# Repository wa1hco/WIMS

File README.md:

# WS Hub

WS Hub (formerly WIMS, the WSJT-X Instance Management System) is one console for a station running several copies of WSJT-X. It gathers every decode into one ranked **call roster**, marks what your goal still needs, and lets one operator answer a station with a click. It works alongside N1MM Logger+, GridTracker, DX cluster spots, and rotators.

It is built for multi-multi VHF contesting (the ARRL VHF contests at W2SZ), and it is useful at home with one radio too: a contest, an award such as DXCC or VUCC, or just a checklist of what is worth working.

**A person starts every transmit.** WS Hub never calls CQ and never transmits on its own. Clicking a roster line answers a station that WSJT-X has already decoded; Enable TX and CQ stay in WSJT-X. It also keeps radios that share an antenna or band from transmitting at the same time.

*The Operate page (an October screenshot, before the WS Hub name and the Show menu).*

## Install

Download the newest release from **[GitHub Releases](https://github.com/wa1hco/WS-Hub/releases)**. The files are still named `wims-<version>-…`.

- **Linux:** unpack the `.tar.gz` anywhere, open **scripts**, and double-click **Install WS Hub**. If the file manager asks, choose **Allow Launching** (or Execute, or Run). WS Hub copies itself to `~/.local/share/ws-hub`; delete the download, then double-click **WS Hub**.
- **Windows:** extract the `.zip` to `C:\WIMS`, open `scripts\windows`, and double-click **Install-Wims.cmd**. Then double-click **WS Hub** on the Desktop.

Step by step, with what to do when the desktop asks a question: **[INSTALL.md](INSTALL.md)**. Updates come from the **Updates** list in the WS Hub window.

## What it does today

- **Call roster** on the Operate page: every decode from every WSJT-X, ranked by score, with Country, distance, and heading. A badge says why a station is needed (grid, state, DXCC, CQ zone, ITU zone, continent, or call); in a contest it says **mult**. Click a line to **Work** that station in the WSJT-X that heard it; **Halt TX** stops what your console started.
- **Goals:** a contest, an award (DXCC, Worked All States, VUCC), a checklist, or your own list, checked against the log you choose. WS Hub reads logs and never changes them.
- **Spotted:** DX cluster spots the goal still needs, on any band, filtered by mode (SSB, CW, FT8, FT4, Other). A spot on a band with no WSJT-X running is marked **QSY**. A click selects the station; it does not retune or transmit yet.
- **Headings:** from the grid when one is known; otherwise an approximate heading from the station's country, marked `~`. WS Hub never guesses a grid square.
- **N1MM:** digital contacts go into N1MM, and N1MM's log decides dupes and mults.
- **Transmit interlock:** radios in one group never transmit together, and an SSB/CW key line can hold a patched WSJT-X off the air.
- **Rotators:** headings are read through hamlib `rotctld`.

What is planned and not built yet (for example, a spot click that retunes the radio and points the antenna) is in **[the build status](docs/plan/wims_status.md)**.

## Documentation

| For | Read |
|--|--|
| Installing | [INSTALL.md](INSTALL.md) |
| Using the console | [User manual](docs/User-manual.md) |
| Setting up WSJT-X, N1MM, and the key line | [Operator setup](docs/operator_setup.md) |
| Trying it at home, step by step | [Tester quick start](docs/tester_quickstart.md) · [What each piece is](docs/tester_roles.md) |
| Every file you can double-click | [scripts/README.md](scripts/README.md) |
| Networking a multi-PC station | [Networking](docs/plan/wims_networking.md) |
| How it is designed, and what is built | [Design](docs/plan/wims_design.md) · [Build status](docs/plan/wims_status.md) |
| What changed in each version | [Release notes](docs/releases/) |

Inside the program, the code, folders, and files still use the old name `wims` (for example `src/wims` and `C:\WIMS`). That is expected.

## Developer

For people changing WS Hub. Operators use the desktop icon.

WS Hub is plain Python 3.10+ with no packages to install. The code is in `src/`. From a clone of [wa1hco/WS-Hub](https://github.com/wa1hco/WS-Hub):

```bash
export PYTHONPATH=$PWD/src   # the launch scripts in scripts/ set this themselves
python3 -m wims version
python3 -m wims solo --no-open
tools/dev/validate.sh        # the same checks CI runs
```

On a Mac there is no double-click installer; from the folder run `scripts/add-wims-to-desktop.sh`. Cutting a release: [INSTALL.md](INSTALL.md#cut-a-release-maintainers). Rules for changes (safety, wording, tests): [docs/project_rules.md](docs/project_rules.md).

## License

WS Hub is free software under the **GNU General Public License v3.0 or later** (GPL-3.0-or-later). See [LICENSE](LICENSE).

    Copyright (C) 2026 Jeff Millar, WA1HCO

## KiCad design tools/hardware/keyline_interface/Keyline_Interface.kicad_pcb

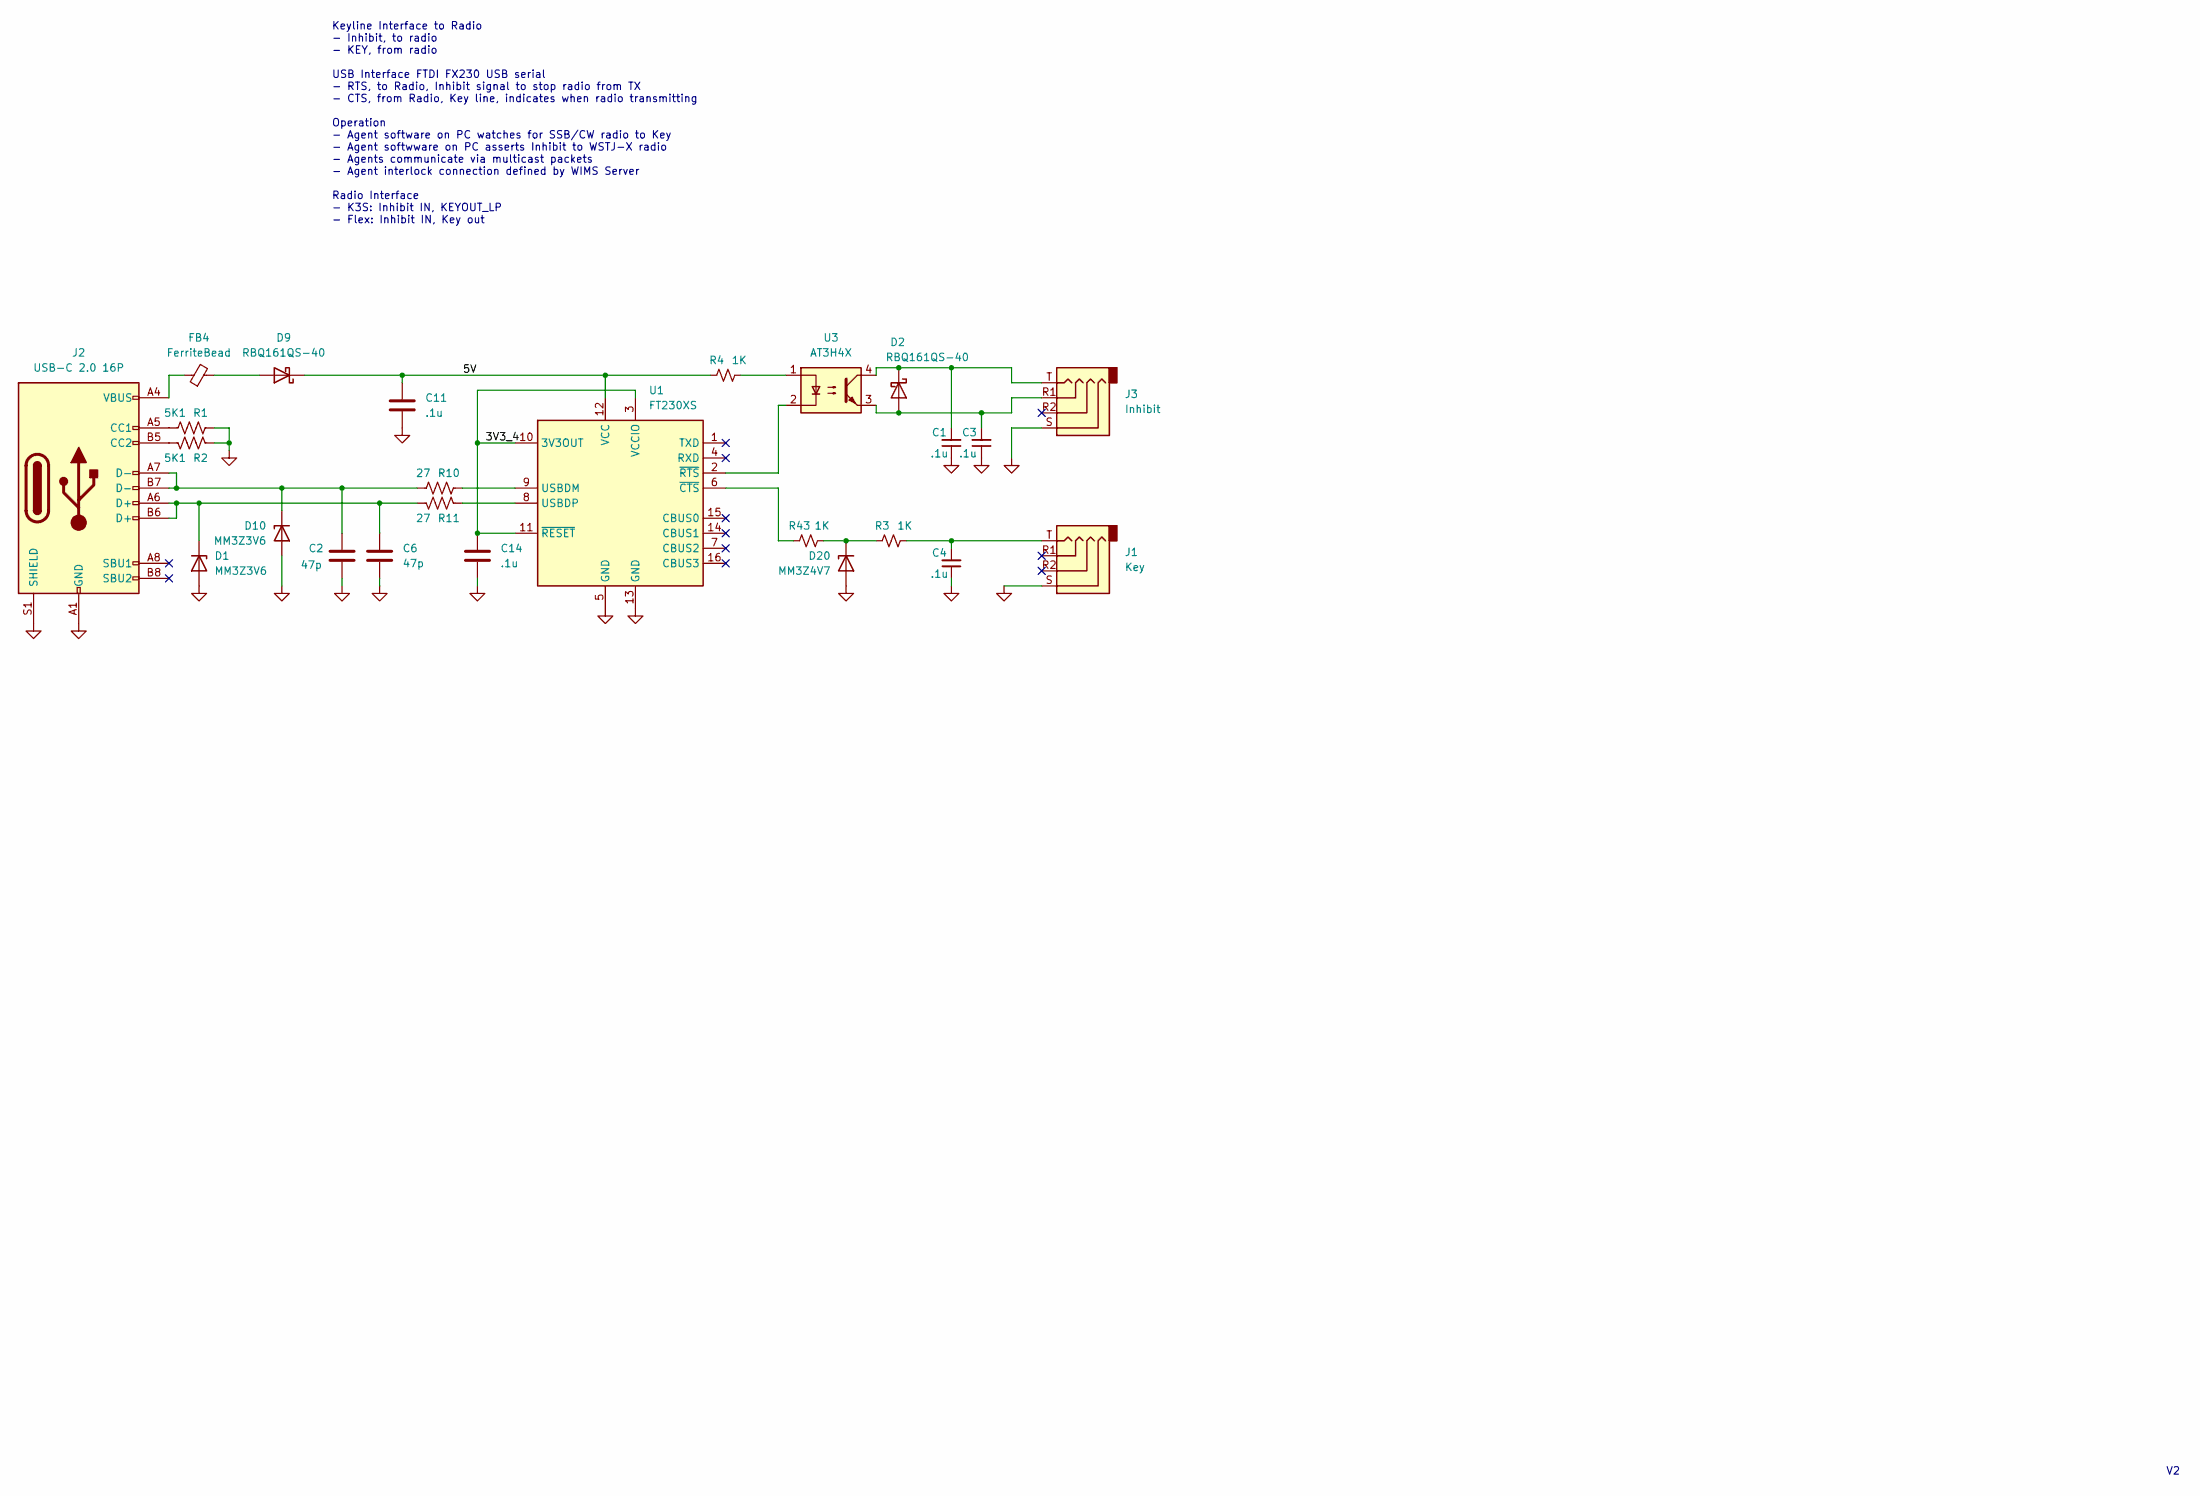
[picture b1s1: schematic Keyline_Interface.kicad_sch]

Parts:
C1, C3, C4: .1u; C_0402_1005Metric
C2, C6: 47p; C_0402_1005Metric; LCSC PN C1671
C11, C14: .1u; C_0402_1005Metric; LCSC PN C15849
D1, D10: MM3Z3V6; D_SOD-323; LCSC PN C19077454
D2, D9: RBQ161QS-40; D_0402_1005Metric
D20: MM3Z4V7; D_SOD-323; LCSC C116949
FB4: FerriteBead; L_0805_2012Metric; LCSC PN C1017
J1: Key; Jack_3.5mm_PJ320E_Horizontal
J2: USB-C 2.0 16P; USB_C_Receptacle_G-Switch_GT-USB-7010ASV; LCSC PN C2835315
J3: Inhibit; Jack_3.5mm_PJ320E_Horizontal
R1, R2: 5K1; R_0402_1005Metric; LCSC PN C23186
R3, R4, R43: 1K; R_0402_1005Metric; LCSC C21190
R10, R11: 27; R_0402_1005Metric; LCSC PN C25190
U1: FT230XS; SSOP-16_3.9x4.9mm_P0.635mm; LCSC PN C69082
U3: AT3H4X; SSOP-4_4.4x2.6mm_P1.27mm

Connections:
/3V3_4: C14.1, U1.3 (VCCIO), U1.10 (3V3OUT), U1.11 (~RESET)
/5V: C11.1, D9.1 (K), R4.2, U1.12 (VCC)
GND: C1.1, C2.2, C3.1, C4.1, C6.2, C11.2, C14.2, D1.2 (A), D10.2 (A), D20.2 (A), J1.S, J2.A1 (GND), J2.A12 (GND), J2.B1 (GND), J2.B12 (GND), J2.S1 (SHIELD), J3.S, R1.1, R2.1, U1.5 (GND), U1.13 (GND)
unnamed: C4.2, J1.T, R3.1
unnamed: C6.1, D1.1 (K), J2.A6 (D+), J2.B6 (D+), R11.2
unnamed: C3.2, D2.2 (A), J3.R1, U3.3
unnamed: C1.2, D2.1 (K), J3.T, U3.4
unnamed: D9.2 (A), FB4.2
unnamed: C2.1, D10.1 (K), J2.A7 (D-), J2.B7 (D-), R10.2
unnamed: D20.1 (K), R3.2, R43.1
unnamed: FB4.1, J2.A4 (VBUS), J2.A9 (VBUS), J2.B4 (VBUS), J2.B9 (VBUS)
unnamed: J2.A5 (CC1), R1.2
unnamed: J2.B5 (CC2), R2.2
unnamed: R4.1, U3.1
unnamed: R10.1, U1.9 (USBDM)
unnamed: R11.1, U1.8 (USBDP)
unnamed: R43.2, U1.6 (~CTS)
unnamed: U1.2 (~RTS), U3.2

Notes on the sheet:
Keyline Interface to Radio - Inhibit, to radio - KEY, from radio USB Interface FTDI FX230 USB serial - RTS, to Radio, Inhibit signal to stop radio from TX - CTS, from Radio, Key line, indicates when radio transmitting Operation - Agent software on PC watches for SSB/CW radio to Key - Agent softwwar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

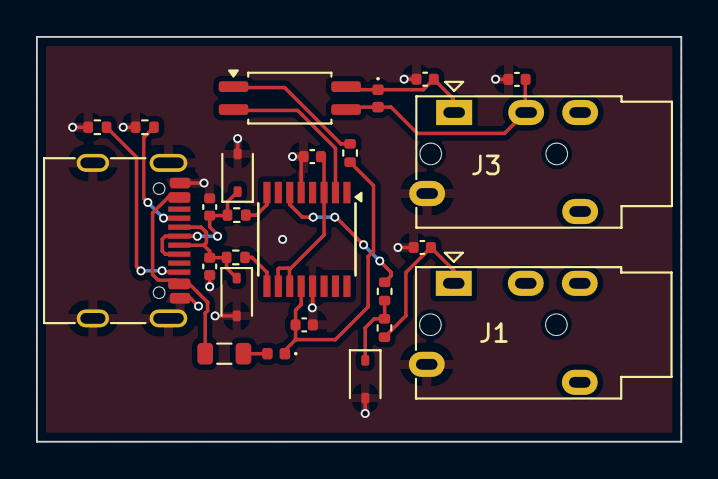
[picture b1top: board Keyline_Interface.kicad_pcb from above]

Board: 2 copper layers, 35.8 x 22.5 mm, 25 parts (0 on the bottom side), 18 nets.

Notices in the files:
tools/hardware/keyline_interface/Keyline_Interface.kicad_pcb:
License CC BY-SA
